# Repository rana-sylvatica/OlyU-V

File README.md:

# OlyU

The OlyU-V is a variant of the OlyU-Small (which, in turn, is a variant of the Model-U).

The OlyU-V is designed for PhoZL and PhobGCCv2.0.3+ to allow for USB data connection, GCC comms, and PhobVision composite video output over a 24-pin USB C connector. 

To access the PhobVision capability, you will need both a PhobGcc equipped with the OlyU-V breakout board as well as the Phongle board **(add link)** and a superspeed-capable USB C to C cable.

To install the OlyU-V in a standard PhobGcc controller, follow the instructions further down on the page and in addition run a wire from the PhobVision video out pin on the PhobGcc motherboard to the pin on the OlyU-V on the end farthest from the USB port.

## (The below images are from the OlyU for context and ordering information but are not exactly the same as the OlyU-V)

### Type 1 - OlyU-Small

### Type 2 - OlyU-Big

# Overview
Both of these boards feature 8 pads. 6 of these pads connect to the GameCube Controller's standard 6 connections for the main cable. The other 2 pads are for USB Data + and -
The shape and alignment of these pads are designed so that installation is easy and does not require any wire stretching across the board. These boards are compatible with PhobGCC and OEM gamecube controllers, but the USB data pins are specifically designed for the PhobGCC and PhoZL (https://github.com/sean44104/phozl)

### Install

# PCB Differences
The OlyU small version is designed to be installed so that the USB-C port is sandwiched between the main pcb and the OlyU pcb. This way, you can use 2mm pin headers for the installation. It has also been reshaped to perfectly fit with the Gamecube Ultimate's shell design

The OlyU big version is shaped just like a standard Model-U. Instead of the USB-C port being in between the 2 PCBs, the order goes PCB,PCB,Port. The PCB is designed this way to allow for easy installation into OEM Gamecube Shells with minimal cutting. However, this makes installation slightly more tricky

Both boards have their USB Data pads aligned perfectly with the main PhoZL and PhobGCC PCB

# NOTE
When ordering these boards on JLCPCB, make sure that your SMT Assembly is BOTTOM for OlyU-Small and TOP for OlyU-Big. Every other setting can be left default, and the finish can be whatever you prefer

# License
This project is licenced under the GNU GPL Version 3. [See the included LICENSE file for details](LICENSE).

# Crane's Lab

Model-U is a circuit board for adding USB-C to custom controllers originally created by Crane.
Please support him here:
https://www.paypal.com/donate/?hosted_button_id=NFDEML5FKR8N8

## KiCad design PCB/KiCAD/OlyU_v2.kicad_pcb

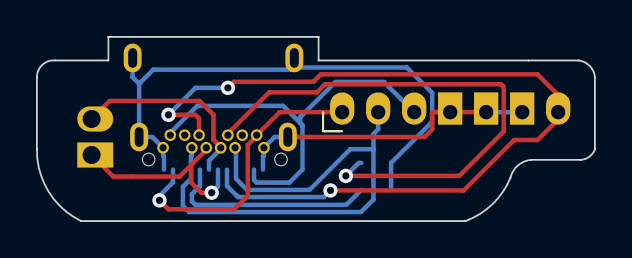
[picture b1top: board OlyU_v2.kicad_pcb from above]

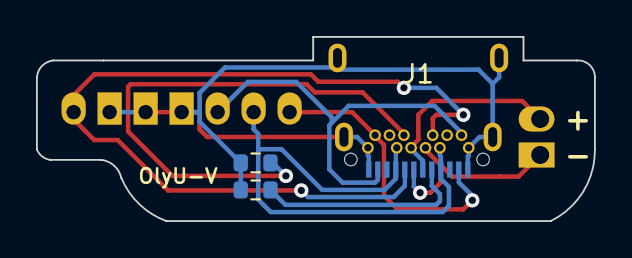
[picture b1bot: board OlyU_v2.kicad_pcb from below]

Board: 2 copper layers, 31.0 x 10.2 mm, 5 parts (4 on the bottom side), 9 nets.

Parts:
J1: USB_C_Receptacle; Shou Han Type-C 24P QCHT
J2: Conn_01x07; PinHeader_1x07_P2.00mm_Vertical
J3: Conn_01x02; PinHeader_1x02_P2.00mm_Vertical
R1, R2: 5.1k; R_0603_1608Metric

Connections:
3V3: J1.A2, J1.B2, J2.1
D3V: J1.A11, J1.B11, J2.3
D+: J1.A6, J1.B6, J3.2
D-: J1.A7, J1.B7, J3.1
GND: J1.A1, J1.A12, J1.B1, J1.B12, J1.S1, J2.4, J2.5, J2.6, R1.1, R2.2
unnamed: J1.A5, R1.2
unnamed: J1.B5, R2.1
PhobVision: J1.A8, J1.B8, J2.7
VBUS: J1.A4, J1.A9, J1.B4, J1.B9, J2.2

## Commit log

2023-01-29 Add OlyU-V files
